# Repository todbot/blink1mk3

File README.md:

# blink(1) mk3 -- USB RGB LED notification light

This repo lives at https://github.com/todbot/blink1mk3

blink(1) mk3 is a blink(1) USB device: https://blink1.thingm.com

"[blink(1) mk3](https://blink1.thingm.com/) is an update to blink(1).
blink(1) is a super status light:
it packs three dimensions of information
(color, brightness and pattern) into a single tiny package that fits into
any USB port on nearly every device. It makes it incredibly easy to connect
any data source in the cloud or on your computer to a full-color RGB LED so
you can know what's happening without checking any windows, going to any
websites or typing any commands." - Get a blink(1) at https://buy.thingm.com/

More technically, blink(1) is a Smart LED controller with built-in USB firmware. blink(1) has a huge range of support from the Linux kernel to Node.js.

This repo contains:

- firmware -- blink(1) firmware for blink1mk3 (on DEFM32HG309F64, same as Tomu)
- bootloader -- DFU firmware for blink(1), based on tomu-bootloader
- schematic -- schematic diagrams of blink(1) mk3

The official repositories for blink(1) software are:

| repository | description |
| ---------- | ----------- |
| [Blink1Control2](https://github.com/todbot/Blink1Control2) | Graphical app for Mac / Windows / Linux |
| [blink1-tool](https://github.com/todbot/blink1-tool) | Command-line tools & C-library for all platforms |
| [blink1-java](https://github.com/todbot/blink1-java) | Java and Processing library |
| [blink1-python](https://github.com/todbot/blink1-python) | Python library |
| [node-blink1](https://github.com/sandeepmistry/node-blink1) | Node.js library |
| [blink1](https://github.com/todbot/blink1) | Hardware/firmware design for mk1/mk2, misc docs & notes
| [blink1mk3](https://github.com/todbot/blink1mk3) | Hardware/firmware design for mk3

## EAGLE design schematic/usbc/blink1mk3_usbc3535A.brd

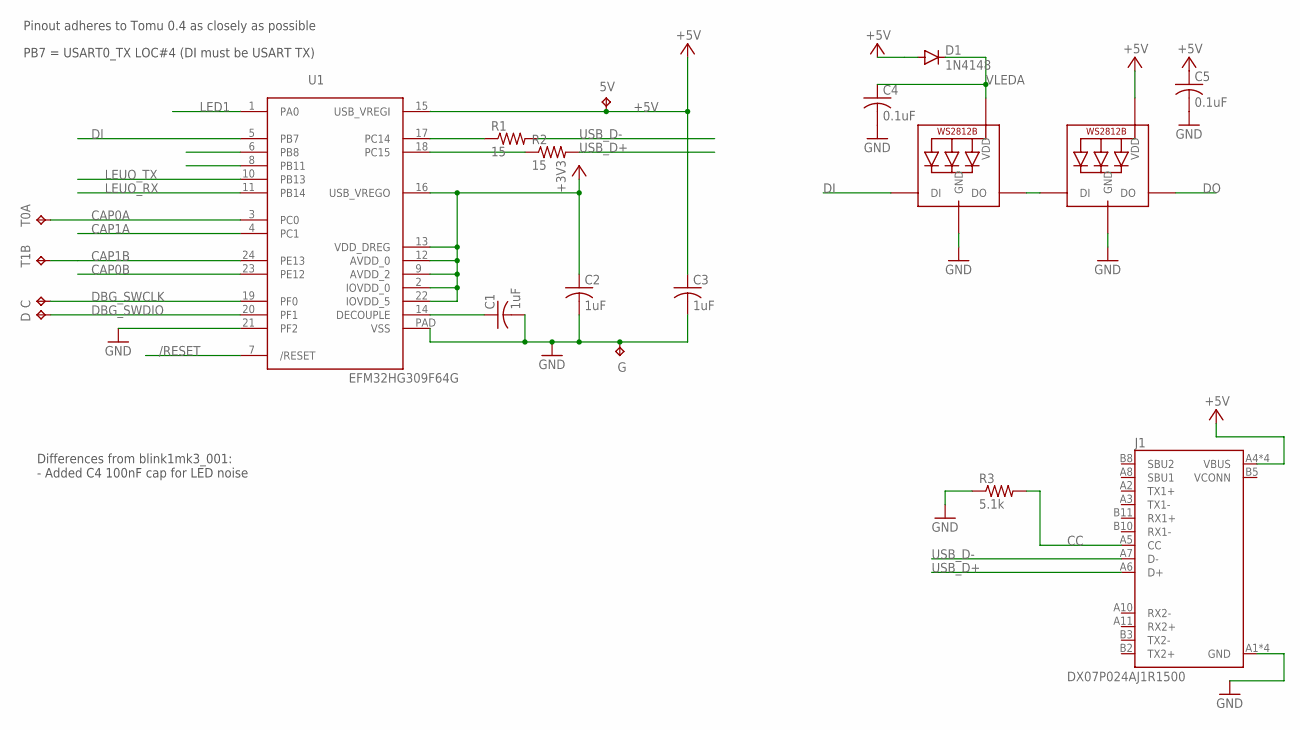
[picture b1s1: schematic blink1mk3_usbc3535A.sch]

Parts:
5V: TPTP10R; TP10R
C: TPTP10R; TP10R
C1, C2, C3: 1uF; C0402
C4, C5: 0.1uF; C0402
D: TPTP10R; TP10R
D1: 1N4148; SOD523
G: TPTP10R; TP10R
J1: DX07P024AJ1R1500; JAE_DX07P024AJ1R1500
LED1: WS2812B3535; LED3535
LED2: SK6812MINI; LED3535
R1, R2: 15; R0402
R3: 5.1k; R0402
T0A, T1B: TPTP10R; TP10R
U1: EFM32HG309F64G; QFN24PAD

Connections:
+3V3: C2.1, U1.2 (IOVDD_0), U1.9 (AVDD_2), U1.12 (AVDD_0), U1.13 (VDD_DREG), U1.16 (USB_VREGO), U1.22 (IOVDD_5)
+5V: 5V.TP, C3.1, C5.1, D1.A, J1.A4 (VBUS), J1.A9 (VBUS), J1.B4 (VBUS), J1.B9 (VBUS), LED2.2 (VDD), U1.15 (USB_VREGI)
/RESET: U1.7 (/RESET)
CAP0A: T0A.TP, U1.3 (PC0)
CAP0B: U1.23 (PE12)
CAP1A: U1.4 (PC1)
CAP1B: T1B.TP, U1.24 (PE13)
CC: J1.A5 (CC), R3.2
DBG_SWCLK: C.TP, U1.19 (PF0)
DBG_SWDIO: D.TP, U1.20 (PF1)
DECOUPLE: C1.1, U1.14 (DECOUPLE)
DI: LED1.1 (DI), U1.5 (PB7)
DO: LED2.3 (DO)
GND: C1.2, C2.2, C3.2, C4.2, C5.2, G.TP, J1.A1 (GND), J1.A12 (GND), J1.B1 (GND), J1.B12 (GND), LED1.4 (GND), LED2.4 (GND), R3.1, U1.21 (PF2), U1.PAD (VSS)
LED1: U1.1 (PA0)
LEUO_RX: U1.11 (PB14)
LEUO_TX: U1.10 (PB13)
unnamed: LED1.3 (DO), LED2.1 (DI)
RUSB_D+: R2.1, U1.18 (PC15)
RUSB_D-: R1.1, U1.17 (PC14)
USB_D+: J1.A6 (D+), R2.2
USB_D-: J1.A7 (D-), R1.2
VCONN: J1.B5 (VCONN)
VLEDA: C4.1, D1.C, LED1.2 (VDD)

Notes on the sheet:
PB7 = USART0_TX LOC#4 (DI must be USART TX)
Pinout adheres to Tomu 0.4 as closely as possible
Differences from blink1mk3_001: - Added C4 100nF cap for LED noise

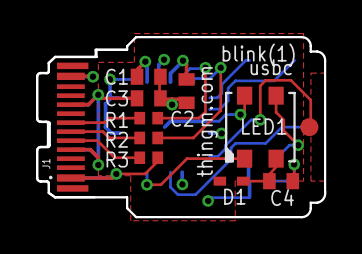
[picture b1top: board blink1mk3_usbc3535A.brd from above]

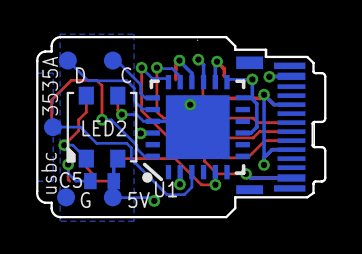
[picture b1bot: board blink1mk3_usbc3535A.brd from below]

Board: 4 copper layers, 16.0 x 10.0 mm, 19 parts (8 on the bottom side), 16 nets.

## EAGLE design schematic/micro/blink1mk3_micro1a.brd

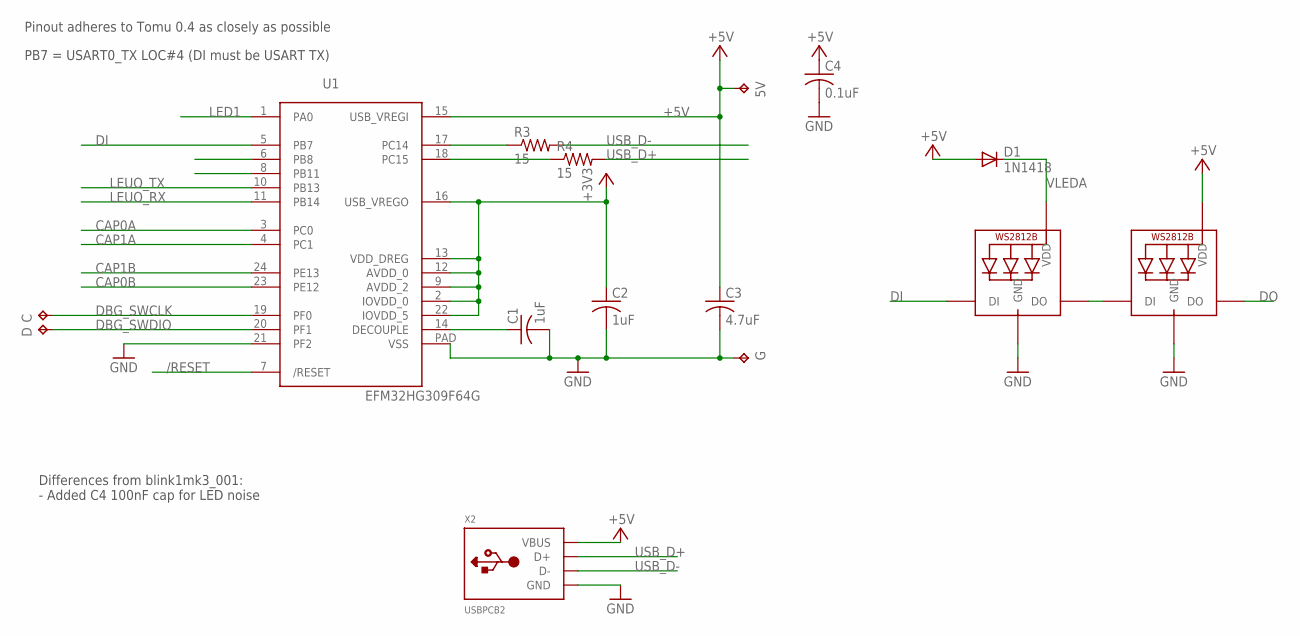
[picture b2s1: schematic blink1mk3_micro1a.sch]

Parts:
5V: TPTP10R; TP10R
C: TPTP10R; TP10R
C1, C2: 1uF; C0402
C3: 4.7uF; C0402
C4: 0.1uF; C0402
D: TPTP10R; TP10R
D1: 1N1418; SOD523
G: TPTP10SQ; TP10SQ
LED1, LED2: WS2812B4020SIDE; SK6812-SIDE
R3, R4: 15; R0402
U1: EFM32HG309F64G; QFN24PAD
X2: USBPCB2; USB-A-PCB-2

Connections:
+3V3: C2.1, U1.2 (IOVDD_0), U1.9 (AVDD_2), U1.12 (AVDD_0), U1.13 (VDD_DREG), U1.16 (USB_VREGO), U1.22 (IOVDD_5)
+5V: 5V.TP, C3.1, C4.1, D1.A, LED2.1-VDD (VDD), U1.15 (USB_VREGI), X2.5V (VBUS)
/RESET: U1.7 (/RESET)
CAP0A: U1.3 (PC0)
CAP0B: U1.23 (PE12)
CAP1A: U1.4 (PC1)
CAP1B: U1.24 (PE13)
DBG_SWCLK: C.TP, U1.19 (PF0)
DBG_SWDIO: D.TP, U1.20 (PF1)
DECOUPLE: C1.1, U1.14 (DECOUPLE)
DI: LED1.4-DIN (DI), U1.5 (PB7)
DO: LED2.2-DOUT (DO)
GND: C1.2, C2.2, C3.2, C4.2, G.TP, LED1.3-GND (GND), LED2.3-GND (GND), U1.21 (PF2), U1.PAD (VSS), X2.GND
LED1: U1.1 (PA0)
LEUO_RX: U1.11 (PB14)
LEUO_TX: U1.10 (PB13)
unnamed: LED1.2-DOUT (DO), LED2.4-DIN (DI)
RUSB_D+: R4.1, U1.18 (PC15)
RUSB_D-: R3.1, U1.17 (PC14)
USB_D+: R4.2, X2.USB_P (D+)
USB_D-: R3.2, X2.USB_M (D-)
VLEDA: D1.C, LED1.1-VDD (VDD)

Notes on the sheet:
PB7 = USART0_TX LOC#4 (DI must be USART TX)
Pinout adheres to Tomu 0.4 as closely as possible
Differences from blink1mk3_001: - Added C4 100nF cap for LED noise

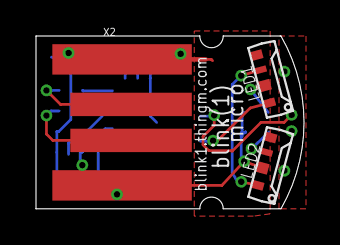
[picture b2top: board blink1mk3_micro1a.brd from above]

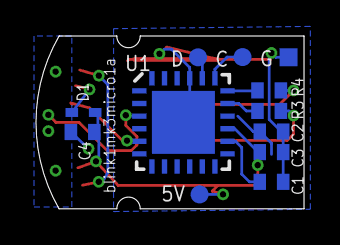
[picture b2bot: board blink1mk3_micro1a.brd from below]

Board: 2 copper layers, 14.9 x 9.6 mm, 15 parts (12 on the bottom side), 13 nets.

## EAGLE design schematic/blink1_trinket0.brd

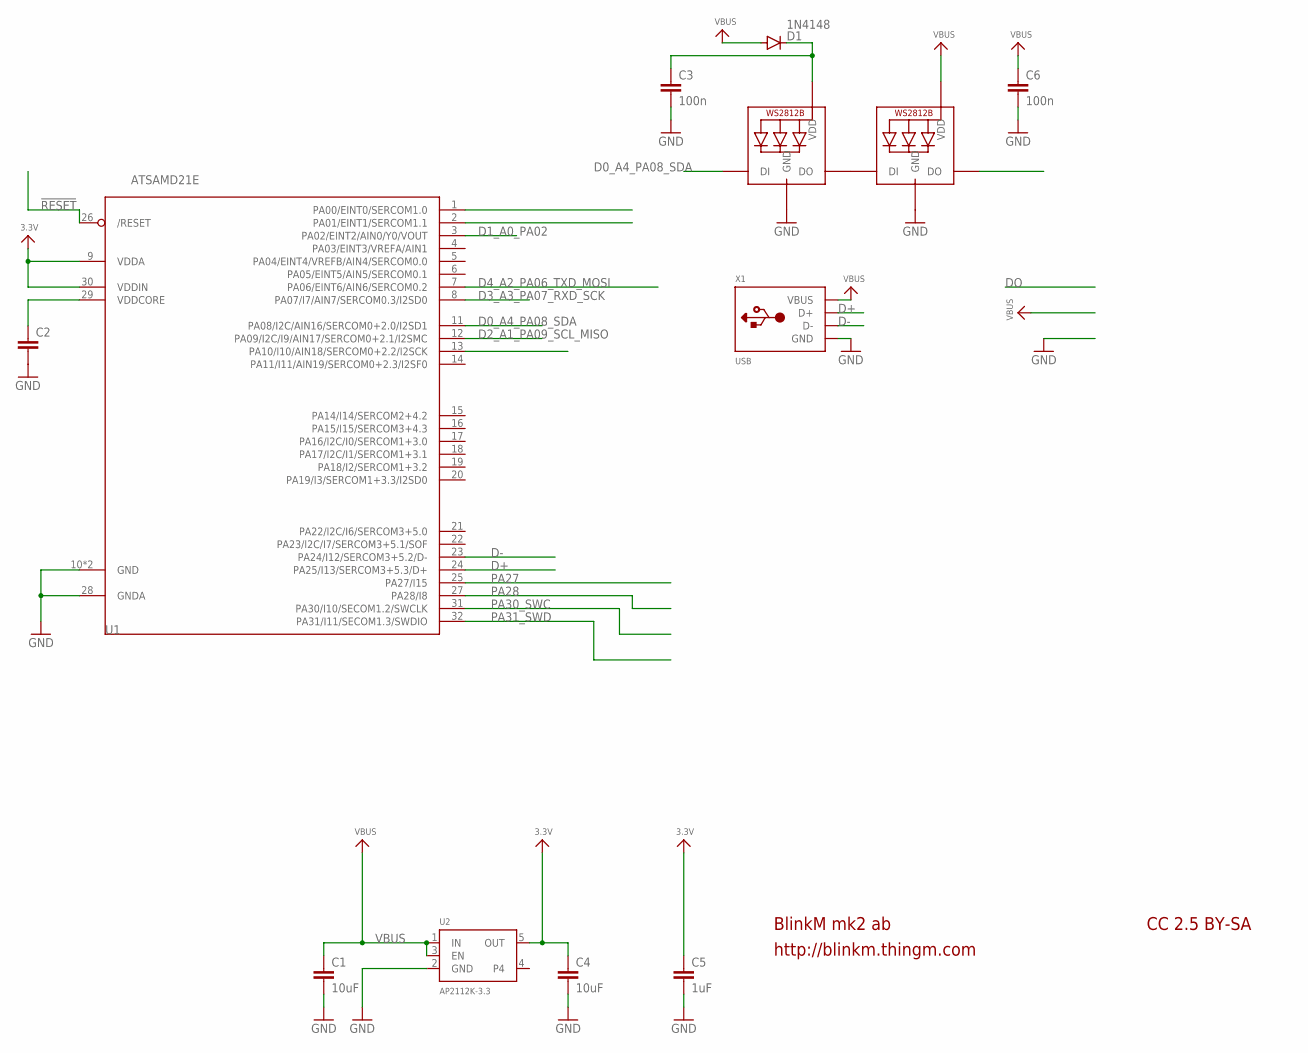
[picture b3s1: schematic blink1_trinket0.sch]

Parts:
C1, C4: 10uF; C0402
C2: C-EUC0402; C0402
C3, C6: 100n; C0402
C5: 1uF; C0402
D1: 1N4148; SOD523
L1, L2: WS2812B3535; LED3535
U1: ATSAMD21E; QFN32_5MM
U2: AP2112K-3.3; SOT23-5
X1: USB; MOLEX-48037-1000

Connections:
3.3V: C4.1, C5.1, U1.9 (VDDA), U1.30 (VDDIN), U2.5 (OUT)
!RESET: U1.26 (/RESET)
A3: U1.1 (PA00/EINT0/SERCOM1.0)
D0_A4_PA08_SDA: L1.1 (DI), U1.11 (PA08/I2C/AIN16/SERCOM0+2.0/I2SD1)
D1_A0_PA02: U1.3 (PA02/EINT2/AIN0/Y0/VOUT)
D2_A1_PA09_SCL_MISO: U1.12 (PA09/I2C/I9/AIN17/SERCOM0+2.1/I2SMC)
D3_A3_PA07_RXD_SCK: U1.8 (PA07/I7/AIN7/SERCOM0.3/I2SD0)
D4_A2_PA06_TXD_MOSI: U1.7 (PA06/EINT6/AIN6/SERCOM0.2)
D+: U1.24 (PA25/I13/SERCOM3+5.3/D+), X1.3 (D+)
D-: U1.23 (PA24/I12/SERCOM3+5.2/D-), X1.2 (D-)
DO: L2.3 (DO)
GND: C1.2, C2.2, C3.2, C4.2, C5.2, C6.2, L1.4 (GND), L2.4 (GND), U1.10 (GND), U1.28 (GNDA), U1.33 (GND), U2.2 (GND), X1.4 (GND)
unnamed: C3.1, D1.C, L1.2 (VDD)
unnamed: L1.3 (DO), L2.1 (DI)
PA27: U1.25 (PA27/I15)
PA28: U1.27 (PA28/I8)
PA30_SWC: U1.31 (PA30/I10/SECOM1.2/SWCLK)
PA31_SWD: U1.32 (PA31/I11/SECOM1.3/SWDIO)
VBUS: C1.1, C6.1, D1.A, L2.2 (VDD), U2.1 (IN), U2.3 (EN), X1.1 (VBUS)
VDDCORE: C2.1, U1.29 (VDDCORE)

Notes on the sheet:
BlinkM mk2 ab
http://blinkm.thingm.com
CC 2.5 BY-SA

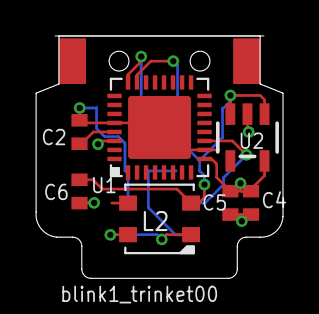
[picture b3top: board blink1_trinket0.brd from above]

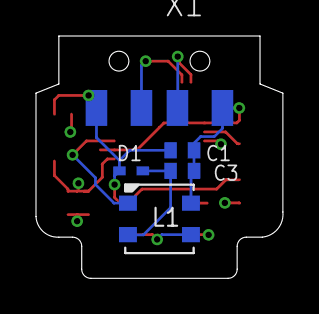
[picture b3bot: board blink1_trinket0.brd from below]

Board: 4 copper layers, 13.7 x 13.5 mm, 12 parts (5 on the bottom side), 9 nets.

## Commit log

2018-03-20 moving schematic over from blink1/hardware/schematic
2018-03-20 actually route all the lines
2018-03-20 fix DI pin so it does not badly interact with tomu firmware
2018-03-21 moved decoupling caps because of bottomside front support
2018-03-21 better pcb layout
2018-03-21 version submitted to oshpark
2018-03-21 first commit of kinda working blink1mk3 firmware
2018-03-22 added blink1mk3_002 schematic
2018-03-22 blink1mk3-test2 added
2018-03-23 implement notes feature so it mostly works
2018-04-02 fixes for toboot and actual efm32HG309F64 board
2018-04-02 refactor a bit, basic blink1 functionality on efm32hg309f64 / tomu
2018-04-03 added iInterface string to descriptor
2018-04-03 added compile-time switch for handleMessage() debug since it can crash the chip
2018-04-04 cleanup descriptors and annotate, and changed HID report usage page
2018-04-06 added BOARD_TYPE_... defines to move between blink1mk3, tomu, efm32hgdevkit
2018-04-08 update doc about changes
2018-04-08 added blink1mk3-test3, but untested
2018-04-08 added size and dfu to Makefile
2018-04-08 adjusted target
2018-04-08 adjust RAM segment to account for toboot_runtime block
2018-04-08 reboot to bootloader works
2018-04-09 added "nm" target to easily see memory map / symbol table
2018-04-09 RAM-based pattern playing seems to work now
2018-04-09 added first attempt at integrating patched tomu-bootloader
2018-04-09 trying to fix submodules
2018-04-09 fix bootloader makefile
2018-04-09 oops fixed bootloader build
2018-04-09 first cut at booster building
2018-04-10 bootloader: added booster to all
2018-04-10 bootloader: fix submodule prep
2018-04-10 firmware: fixed toboot bootloader setup, I think
2018-04-10 bootloader: custom usb descriptor
2018-04-10 bootloader: add BOARD_TYPE_BLINK1 sections, mostly to be filled in later
2018-04-10 added initial README
2018-04-10 pattern saving to flash working correctly now, but had to modify linker script to do it cleanly
2018-04-10 bootloader: added proper GPIO reset for BOARD_TYPE_BLINK1
2018-04-11 bootloader: can now easily program with jlink and openocd via makefile
2018-04-11 bootloader: updated to use ThingM blink(1) DFU vendorId and productId
2018-04-11 Fix Makefile so programming via jlink or openocd works for both firmware and bootloader
2018-04-11 .gitignore updates
2018-04-12 fix comment about AUTORUN and comment out boot_failures return for now
2018-04-12 clean up linker script
2018-04-12 clean up test3 firmware, mostly about flash writing. patternw writing works fine but why does notes writing crash the chip?
2018-04-24 minor cleanup
2018-04-24 added blink1-tool --gobootload to dfu
2018-04-24 blink1 micro: added registration holes, cleanup
2018-05-08 added business card variant, and 3535 LED variant
2018-05-08 card layout update
2018-05-09 sync schematic experiments
2018-05-09 update pcbs with correct filename labels
2018-05-16 added business card idea
2018-05-16 pulled down update to tomu-bootloader
2018-05-16 sync up blink1mk3 bootloader with tomu bootloader changes
2018-05-18 add more micro ideas
2018-05-22 "make dfu" allows blink1-tool to fail (in the case of first programming)
2018-05-22 add note about doing "power on" when using Jlink to do bootloader program
2018-05-22 fix EFM32HG309 pad spacing issue. omg what a slog
2018-05-24 fix QFN footprint again, add blink1mk3_card2
2018-05-24 small blink1mk3_card2 pcb fixes
2018-05-24 added blink1mk3-test4 firmware, fixes first two pattern lines getting nuked problem, adds startup_params datastruct (but no action on it yet)
2018-05-25 updated to latest test
2018-05-25 finally got usernotes working correctly on both Windows and Mac (due to my not understanding report size limitations)
2018-05-26 fixed usernotes flash saving problem (buffer must be word-aligned: SL_ALIGN(4)
2018-05-27 save memory by correctly casting fader atributes
2018-05-29 adjust SDI speed faster for SK6812 timing
2018-05-29 small cleanup and notes
2018-06-11 bootlaoder: trying to fix SWD + SWC pin short to start bootloader
2018-06-11 add hsvtorgb function
2018-06-11 added random boot mode, trying out capsense, currently causes lockups
2018-07-11 disable SWD while reading pins to enable bootloader
2018-07-13 fix up BOARD_ defines
2018-08-03 small bootloader comment addition
2018-08-03 small blink1mk3-test4 comment addition
2018-08-03 added blink1mk3-test5
2018-08-11 blink1mk3-test5 firmware: refactored flash storage for user data (startup params and color patterns). not fully tested
2018-08-11 small readme additions
2018-08-11 schematic directory cleanup
2018-09-11 bootloader: small reminder about power on when testing
2018-09-11 firmware test5: small doc updates
2018-09-11 schematics: added blink1mk3-005t3
2018-09-11 schematic: added blink1mk3_micrco1d2
2018-10-09 added blink1mk3_005t4 pcb
2018-11-15 small blink1 mk3 schematic fixes before release to manufacturing
2018-11-15 added programming jig experiments
2018-11-15 updated gitignore
2018-11-16 small blink1mk3-test5 Makefile fixes
2018-11-16 blink1mk3-test5 added debug.h
2018-11-16 update to latest tomu-bootloader
2018-11-28 update descriptors
2018-11-28 firmware: added bootloader lock
2018-11-28 fixup master makefile
2018-11-28 cleanup makefile and ld a bit
2018-11-28 bootloader: update bootloader to track new toboot
2018-11-28 firmware: new dir for firmware
2018-11-28 pcb: enlarged silkscreen text for seeed
2018-11-29 bootloader: fix product_name
2018-11-29 bootloader: set webusb landing page to dfu.blink1.thingm.com
2018-11-30 firmware: add SWD pins connect checking to reboot to bootloader
2018-11-30 add openocd-stlinkv2, cheap 8 buck SWD programmer!
2018-12-02 firmware: cleaned up hardware SWD pin bootload triggering, small comments added
2018-12-02 bootloader: first cut at ws2812 support
2018-12-02 bootloader: clean up ws2812 toggling
2018-12-02 firmware: made rgb_t {r,g,b}; added more debug
2018-12-02 bootloader: clean up ws2812 setup code
2018-12-02 bootloader: add erase target to Makefile to make bootloader testing easier
2018-12-02 firmware: turn off debug
2018-12-09 fix servertickle/serverdown feature
2018-12-09 servertickle/serverdown code clean
2018-12-14 firmware: debugging startup logic, having issues with copying userData to variables. argh
2018-12-15 firmware: okay startup params back to working I think
2018-12-15 firmware: startup logic rewrite almost done
2018-12-15 firmware: add debug_setup() and debug_ch() to debug.h
2018-12-15 extend sleep before dfu program a bit
2018-12-15 remove debug info in usb descriptor string
2018-12-15 firmware: clarify logic on usb power up, turn off debug, bump version to prod
2018-12-15 add prod ld
2018-12-15 added memory dump target
2018-12-16 rework startup logic, fix serial number, still researching weird hub-related startup issue
2018-12-18 improve serial number generation from chip uniqueid
2018-12-18 add 'U' get chip unique id
2018-12-18 turn off debug
2018-12-19 fixed dir name typo
2018-12-19 added progbin targets, cleaned up other jlink targets
2018-12-19 cleaned up startup playing logic, moved it to updateMisc() instead of updateLEDs()
2018-12-19 extend startup check to 1000ms
2018-12-19 move dir on typo
2019-01-15 schematic mk3_005t5, fix D1 part number
2019-01-15 firmware: rename makefile target to progfull, add pre-erase to process
2019-03-25 added related repo links to README
2019-04-17 updated README a little
2019-07-10 added new mk3 board variations
2019-08-04 added clean-gecko
2019-08-04 fix signature of myputc() for USB_DEBUG
2019-08-04 clarify USB_PWRSAVE_MODE
2019-08-04 Advertise as self-powered (but still needing bus power) instead of bus-powered as work-around to USB suspend causing USB stack to pause chip
2019-08-04 version bump and cleanup
2019-08-04 added sleep to wait for bootloader
2019-08-04 README update
2019-08-04 added changelog
2019-08-04 update firmware readme
2019-08-04 added first pass at fw update tool
2019-08-04 update fw update instructions
2019-08-04 update fw update readme
2019-08-05 fw_update: fix windows bat sleep
2019-08-30 usbc tests
2019-09-17 rename sch 005t6_5050_4l to 005t6_4L
2020-03-07 update firmware updater tools
2020-03-10 more usbc work
2020-03-10 save micro 4l for posterity
2020-03-10 added uncomplete work on 5050-based usbc
2020-03-10 schem reorg
2021-02-13 added 3535 usbc variant
2021-02-16 update usbc3535A board
2021-05-08 make jlink gui go away
2021-05-08 attempt to address startup params issue #8
2021-05-09 create bin-to-dfu target
2021-05-09 attempt to fix startup user params not being copied to main running vars. This is second problem in issue #8

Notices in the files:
parts and their libraries:
microbuilder: This work is placed in the public domain, and may be freely used for commercial and non-commercial work with the following conditions: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
